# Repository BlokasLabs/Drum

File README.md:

# Drum

Drum is the Blokas Edition of the [Bleep Drum](http://bleeplabs.com/store/bleep-drum-midi/). It features a built-in speaker, so the beats won't stop flowing even when there's no headphones or external speaker at hand's reach!

## Building The Source Code

The firmware has dependencies on Bounce2 and MIDI libraries. They can easily be setup from within the Arduino IDE:

1. Go to Sketch -> Include Library -> Manage Libaries...
2. Install the following libraries:
    * [Bounce2](https://github.com/thomasfredericks/Bounce2) by Thomas Ouellet Fredericks with contributions from: Eric Lowry, Jim Schimpf and Tom Harkaway.
    * [MIDI Library](https://github.com/FortySevenEffects/arduino_midi_library) by Forty Seven Effects.

After dependencies are set up, just open DRUM/DRUM.ino in [Arduino IDE](https://www.arduino.cc/en/Main/Software) and it should build successfully.

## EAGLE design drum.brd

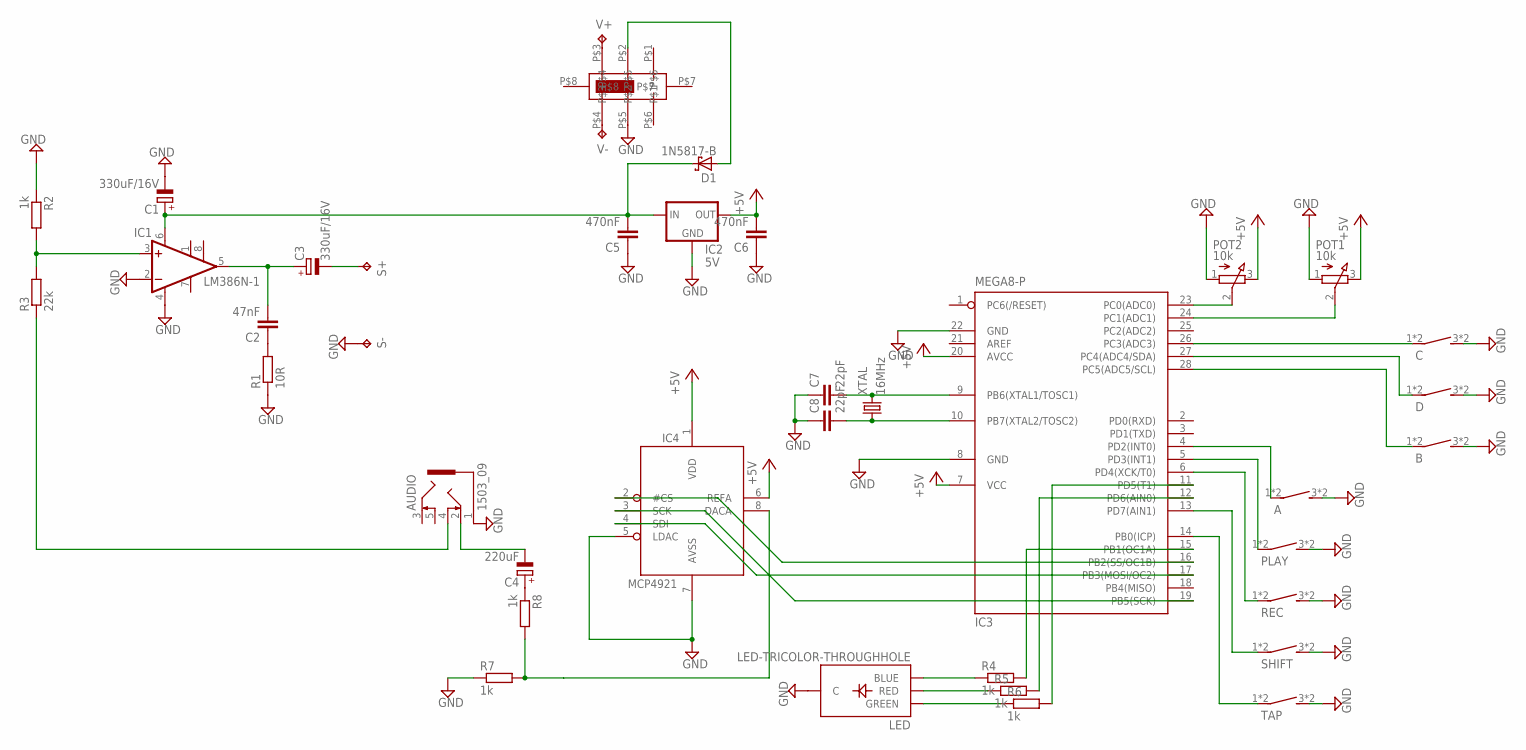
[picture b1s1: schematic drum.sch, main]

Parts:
A: D6R_SPSTB3F-4000; B3F-4000
AUDIO: 1503_09
B: D6R_SPSTB3F-4000; B3F-4000
C: D6R_SPSTB3F-4000; B3F-4000
C1, C3: 330uF/16V; E3,5-8
C2: 47nF; C050-024X044
C4: 220uF; E2,5-6
C5, C6: 470nF; C050-024X044
C7, C8: 22pF; C050-024X044
D: D6R_SPSTB3F-4000; B3F-4000
D1: 1N5817-B; DO41-7.6
IC1: LM386N-1; DIL08
IC2: 5V; 78LXX
IC3: MEGA8-P; DIL28-3
IC4: MCP4921; DIL08
LED: LED-TRICOLOR-THROUGHHOLE
PLAY: D6R_SPSTB3F-4000; B3F-4000
POT1, POT2: 10k; EVUFXJ
PWR: SLIDE_SW_DPDT; SS008B02P22
R1: 10R; 0207/10
R2, R4, R5, R6, R7, R8: 1k; 0207/10
R3: 22k; 0207/10
REC: D6R_SPSTB3F-4000; B3F-4000
S+: TPPAD1-17; P1-17
S-: TPPAD1-17; P1-17
SHIFT: D6R_SPSTB3F-4000; B3F-4000
TAP: D6R_SPSTB3F-4000; B3F-4000
V+: TPPAD1-17; P1-17
V-: TPPAD1-17; P1-17
XTAL: 16MHz; HC49/S

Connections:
+5V: C6.2, IC2.OUT, IC3.7 (VCC), IC3.20 (AVCC), IC4.1 (VDD), IC4.6 (REFA), POT1.3 (E), POT2.3 (E)
GND: A.3 (S), A.4 (S), AUDIO.1, B.3 (S), B.4 (S), C.3 (S), C.4 (S), C1.-, C5.1, C6.1, C7.1, C8.1, D.3 (S), D.4 (S), IC1.2 (-IN), IC1.4 (GND), IC2.GND, IC3.8 (GND), IC3.22 (GND), IC4.5 (LDAC), IC4.7 (AVSS), LED.GND (C), PLAY.3 (S), PLAY.4 (S), POT1.1 (A), POT2.1 (A), PWR.P$5, R1.1, R2.1, R7.1, REC.3 (S), REC.4 (S), S-.TP, SHIFT.3 (S), SHIFT.4 (S), TAP.3 (S), TAP.4 (S)
unnamed: C2.1, R1.2
unnamed: IC3.15 (PB1(OC1A)), R4.2
unnamed: IC3.12 (PD6(AIN0)), R5.2
unnamed: IC3.11 (PD5(T1)), R6.2
unnamed: IC3.5 (PD3(INT1)), PLAY.1, PLAY.2
unnamed: C1.+, C5.2, D1.C, IC1.6 (VS), IC2.IN
unnamed: IC3.17 (PB3(MOSI/OC2)), IC4.4 (SDI)
unnamed: A.1, A.2, IC3.4 (PD2(INT0))
unnamed: IC3.19 (PB5(SCK)), IC4.3 (SCK)
unnamed: IC3.23 (PC0(ADC0)), POT2.2 (S)
unnamed: IC3.24 (PC1(ADC1)), POT1.2 (S)
unnamed: C4.+, R8.1
unnamed: IC4.8 (DACA), R7.2, R8.2
unnamed: LED.GRN (BLUE), R4.1
unnamed: LED.BLU (RED), R5.1
unnamed: LED.RED (GREEN), R6.1
unnamed: C7.2, IC3.9 (PB6(XTAL1/TOSC1)), XTAL.2
unnamed: AUDIO.2, C4.-
unnamed: D.1, D.2, IC3.27 (PC4(ADC4/SDA))
unnamed: C8.2, IC3.10 (PB7(XTAL2/TOSC2)), XTAL.1
unnamed: C2.2, C3.+, IC1.5 (OUT)
unnamed: C3.-, S+.TP
unnamed: IC1.3 (+IN), R2.2, R3.2
unnamed: AUDIO.4, R3.1
unnamed: PWR.P$4, V-.TP
unnamed: PWR.P$3, V+.TP
unnamed: D1.A, PWR.P$2
unnamed: IC3.14 (PB0(ICP)), TAP.1, TAP.2
unnamed: IC3.6 (PD4(XCK/T0)), REC.1, REC.2
unnamed: IC3.13 (PD7(AIN1)), SHIFT.1, SHIFT.2
unnamed: C.1, C.2, IC3.26 (PC3(ADC3))
unnamed: B.1, B.2, IC3.28 (PC5(ADC5/SCL))
unnamed: IC3.16 (PB2(SS/OC1B)), IC4.2 (#CS)

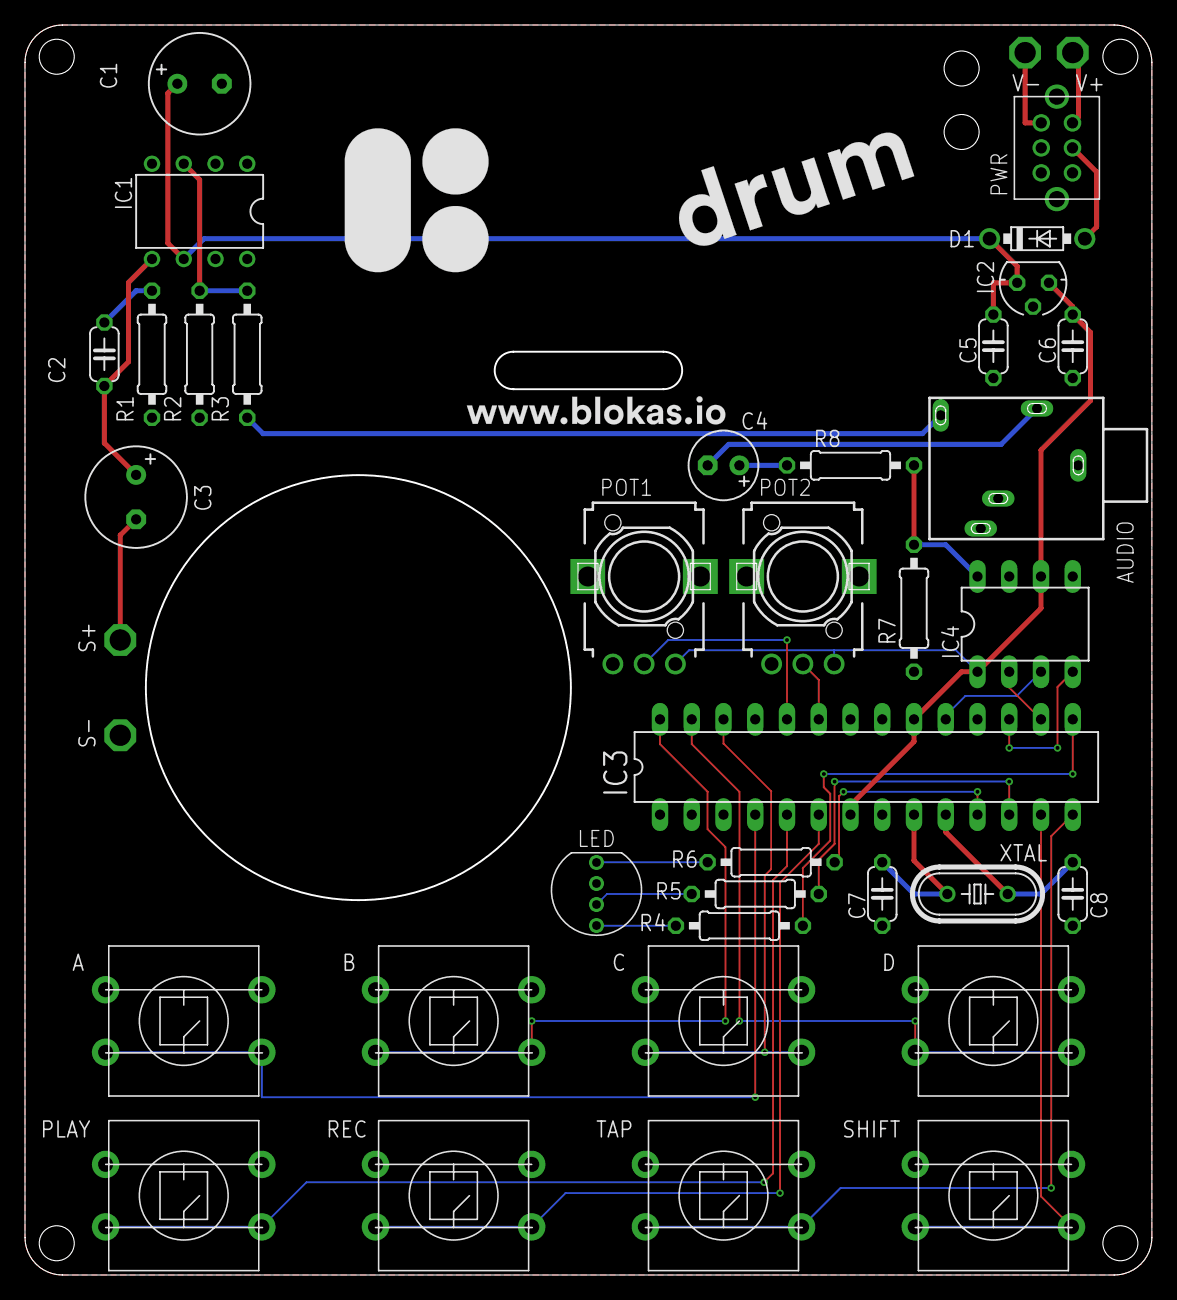
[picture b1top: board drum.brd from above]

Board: 2 copper layers, 90.0 x 99.8 mm, 39 parts (0 on the bottom side), 35 nets.

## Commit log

2017-05-23 Restructuring the repository
2017-05-23 Added license information
2017-05-23 Adding schematics for the board
2017-05-23 Adding README.md
2017-05-23 Renaming LICENSE to LICENSE.md
